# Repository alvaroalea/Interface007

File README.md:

# Interface007
Schematics in KiCad format of a simple interface for 8bits microcomputer ZX Spectrum.

Thanks to flopping for pictures and full schematic.

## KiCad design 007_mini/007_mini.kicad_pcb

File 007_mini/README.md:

# Interface007
Schematics in KiCad format of a simple interface for 8bits microcomputer ZX Spectrum.

Thanks to flopping for pictures and full schematic.

This is a reduced version of PCB with a dip-switch for select between 4 banks of Memory.

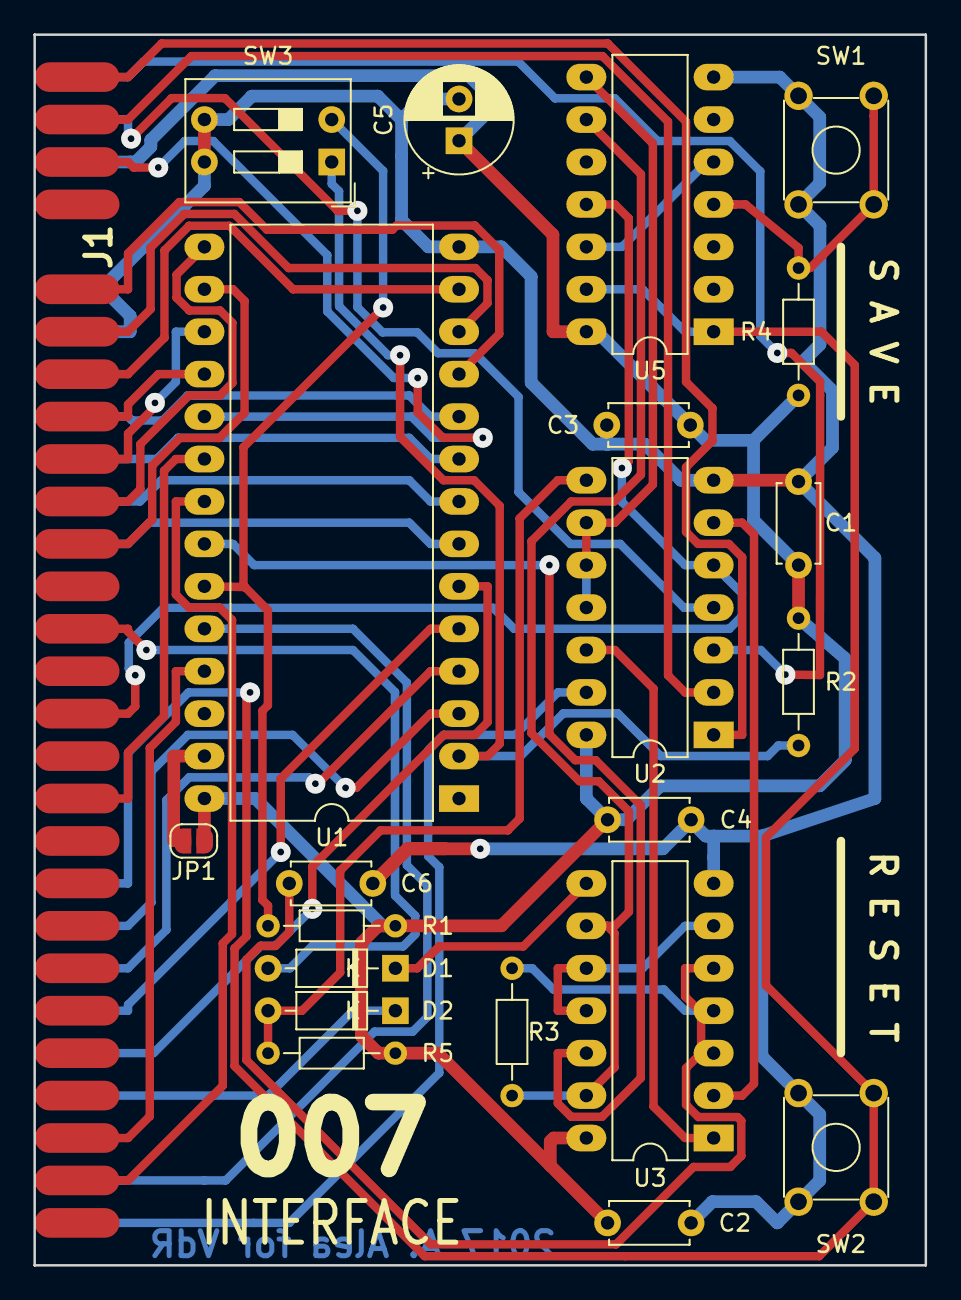
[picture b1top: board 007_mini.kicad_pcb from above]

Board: 2 copper layers, 53.3 x 73.7 mm, 22 parts (0 on the bottom side), 45 nets.

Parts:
C1, C2, C3, C4, C6: 100n; C_Disc_D4.7mm_W2.5mm_P5.00mm
C5: 100uF; CP_Radial_D6.3mm_P2.50mm
D1, D2: 1N4148; D_DO-35_SOD27_P7.62mm_Horizontal
J1: ZX_Spectrum_Connector_48K; ZX_CONN
JP1: SolderJumper_2_Open; SolderJumper-2_P1.3mm_Open_RoundedPad1.0x1.5mm
R1, R2: 10K; R_Axial_DIN0204_L3.6mm_D1.6mm_P7.62mm_Horizontal
R3: 100; R_Axial_DIN0204_L3.6mm_D1.6mm_P7.62mm_Horizontal
R4: 4k7; R_Axial_DIN0204_L3.6mm_D1.6mm_P7.62mm_Horizontal
R5: 330; R_Axial_DIN0204_L3.6mm_D1.6mm_P7.62mm_Horizontal
SW1: SAVE; SW_TH_Tactile_Omron_B3F-10xx
SW2: RESET; SW_TH_Tactile_Omron_B3F-10xx
SW3: SW_DIP_x02; SW_DIP_SPSTx02_Slide_9.78x7.26mm_W7.62mm_P2.54mm
U1: 2764; DIP-28_W15.24mm_LongPads
U2: 74LS27; DIP-14_W7.62mm_LongPads
U3: 74LS10; DIP-14_W7.62mm_LongPads
U5: 74LS74; DIP-14_W7.62mm_LongPads

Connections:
+5V: C1.1, C2.1, C3.1, C4.1, C5.1, J1.A3, JP1.1, R1.1, R2.1, R4.1, R5.1, U1.28, U2.14, U3.14, U5.14
/A0: J1.A9, U1.10
/A1: J1.A10, U1.9
/A2: J1.A11, U1.8
/A3: J1.A12, U1.7
/A4: J1.A24, U1.6
/A5: J1.A23, U1.5
/A6: J1.A22, U1.4
/A7: J1.A21, U1.3
/A8: J1.B26, U1.25
/A9: J1.A27, U1.24
/A10: J1.B27, U1.21
/A11: J1.A28, U2.13
/A12: J1.A2, U2.4
/A13: J1.B2, U2.2
/A14: J1.A1, U2.3
/A15: J1.B1, U2.1
/D0: J1.B6, U1.11
/D1: J1.B7, U1.12
/D2: J1.B8, U1.13
/D3: J1.B11, U1.15
/D4: J1.B12, U1.16
/D5: J1.B10, U1.17
/D6: J1.B9, U1.18
/D7: J1.B3, U1.19
/RD: J1.B18, U1.20
GND: C1.2, C2.2, C3.2, C4.2, C5.2, C6.2, J1.A6, J1.A7, SW1.1, SW1.3, SW2.1, SW2.3, SW3.3, SW3.4, U1.14, U2.7, U3.7, U5.7
MREQ: J1.B16, U2.5, U5.11
NMI: D1.2, J1.B14
unnamed: C6.1, R3.2, U3.3, U3.4, U3.5
unnamed: D1.1, U3.8
unnamed: D2.2, R5.2, U2.8
unnamed: JP1.2, U1.27
unnamed: R3.1, U3.9, U3.13, U5.9
unnamed: R4.2, SW1.2, SW1.4, U5.4
unnamed: U1.22, U3.12
unnamed: U2.6, U3.2
unnamed: U2.9, U2.10, U2.11, U5.8
unnamed: U2.12, U3.1
unnamed: U3.6, U3.10, U3.11
unnamed: U5.5, U5.12
RESET: J1.A20, SW2.2, SW2.4, U5.1, U5.13
ROMA11: R1.2, SW3.2, U1.23
ROMA12: R2.2, SW3.1, U1.2
ROMCS: D2.1, J1.A25

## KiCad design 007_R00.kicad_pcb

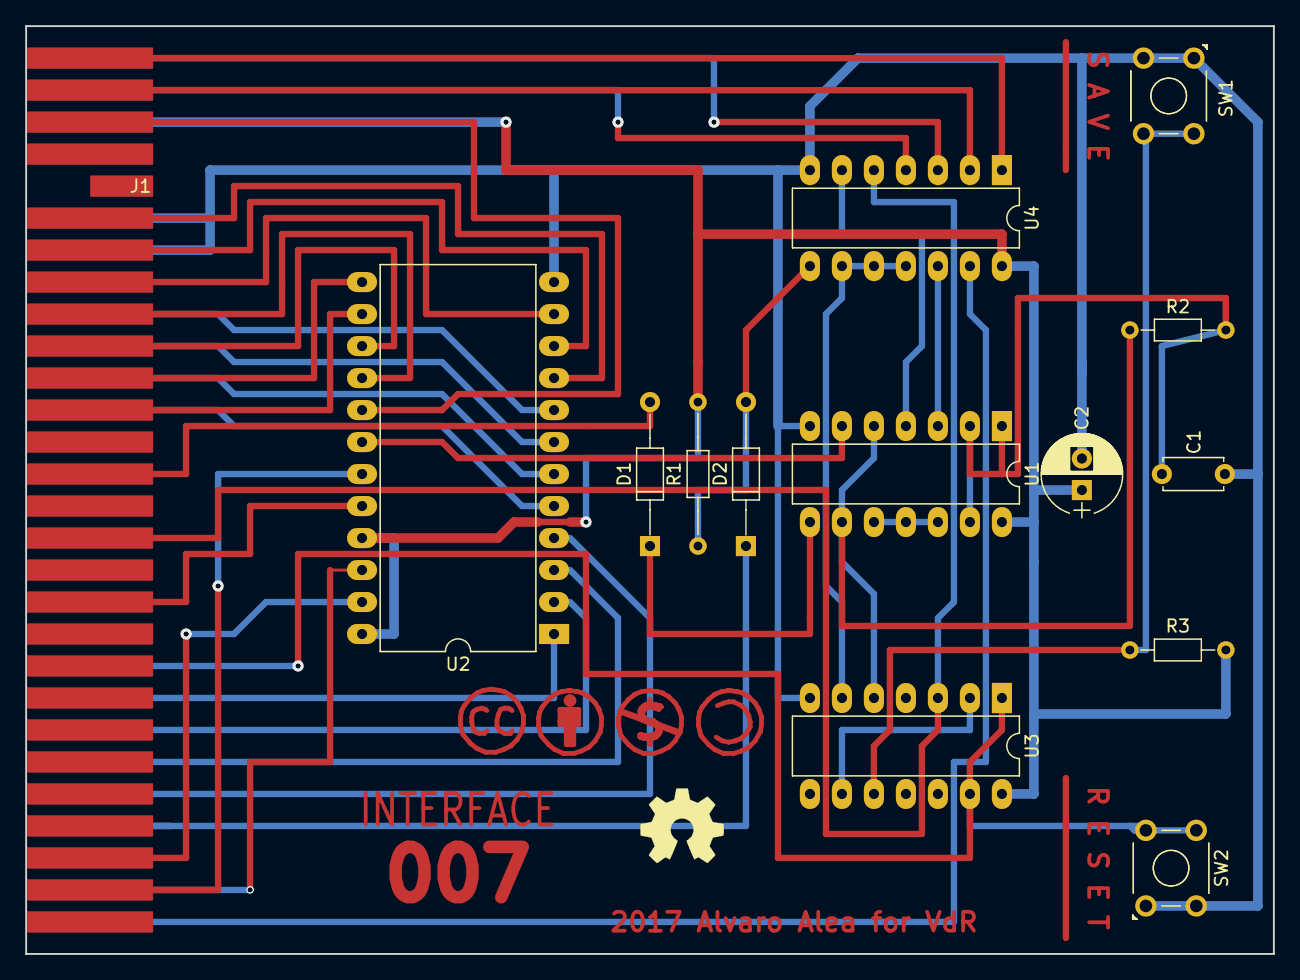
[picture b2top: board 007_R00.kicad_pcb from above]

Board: 2 copper layers, 99.1 x 73.7 mm, 14 parts (0 on the bottom side), 42 nets.

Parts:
C1: 100n; C_Disc_D4.7mm_W2.5mm_P5.00mm
C2: 100uF; CP_Radial_D6.3mm_P2.50mm
D1, D2: 1N4148; D_DO-35_SOD27_P11.43mm_Horizontal
J1: CONN_02X28; PCB_Edge_Lateral_2x28_Pitch2.54mm
R1: 330; R_Axial_DIN0204_L3.6mm_D1.6mm_P11.43mm_Horizontal
R2: 100; R_Axial_DIN0204_L3.6mm_D1.6mm_P7.62mm_Horizontal
R3: 4k7; R_Axial_DIN0204_L3.6mm_D1.6mm_P7.62mm_Horizontal
SW1: SAVE; SW_TH_Tactile_Omron_B3F-10xx
SW2: RESET; SW_TH_Tactile_Omron_B3F-10xx
U1: 74LS10; DIP-14_W7.62mm_LongPads
U2: 2716; DIP-24_W15.24mm_LongPads
U3: 74LS74; DIP-14_W7.62mm_LongPads
U4: 74LS27; DIP-14_W7.62mm_LongPads

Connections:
+5V: C2.1, J1.5, R1.1, R3.1, U1.14, U2.21, U2.24, U3.14, U4.14
/A0: J1.17, U2.8
/A1: J1.19, U2.7
/A2: J1.21, U2.6
/A3: J1.23, U2.5
/A4: J1.47, U2.4
/A5: J1.45, U2.3
/A6: J1.43, U2.2
/A7: J1.41, U2.1
/A8: J1.52, U2.23
/A9: J1.53, U2.22
/A10: J1.54, U2.19
/A11: J1.55, U4.13
/A12: J1.3, U4.4
/A13: J1.4, U4.2
/A14: J1.1, U4.3
/A15: J1.2, U4.1
/D0: J1.12, U2.9
/D1: J1.14, U2.10
/D2: J1.16, U2.11
/D3: J1.22, U2.13
/D4: J1.24, U2.14
/D5: J1.20, U2.15
/D6: J1.18, U2.16
/D7: J1.6, U2.17
/EPROMOE: U1.6, U2.18
/MREQ: J1.32, U3.3, U4.5
/NMI: D1.2, J1.28
/RD: J1.36, U2.20
/RESET: J1.39, SW2.2, SW2.4, U3.1, U3.13
/ROMCS: D2.1, J1.49
GND: C1.2, C2.2, J1.11, J1.13, SW1.1, SW1.3, SW2.1, SW2.3, U1.7, U2.12, U3.7, U4.7
unnamed: C1.1, R2.2, U1.1, U1.2, U1.13
unnamed: D1.1, U1.8
unnamed: D2.2, R1.2, U4.8
unnamed: R2.1, U1.5, U1.9, U3.5
unnamed: R3.2, SW1.2, SW1.4, U3.10
unnamed: U1.3, U4.12
unnamed: U1.4, U4.6
unnamed: U1.10, U1.11, U1.12
unnamed: U3.2, U3.9
unnamed: U3.6, U4.9, U4.10, U4.11

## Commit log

2017-05-29 Add Initial files via upload
2017-06-02 with edge conector
2017-06-02 Update LICENSE
2018-07-13 pcb mini
2018-07-13 mini pcb
2018-07-22 fix push buttons
2022-09-27 me habia olvidado de la rom
2022-11-08 add rom files
